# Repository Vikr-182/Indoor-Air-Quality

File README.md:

# Indoor-Air-Quality-Management
A complete Air Quality Index (AQI) sensing and management system designed and deployed in houses, to analyze the effects of outdoor and indoor events on indoor air quality, along with a Twitter service for constant updates.

## Components Involved
We list one by one, all the components involved in the usage -
- Using Microcontroller ESP8266
- Designing the 3D Enclosure
- Collecting and Analyzing Data
- Twitter Alerts
- OneM2M Usage

## Desigining the case
We designed the enclosure for our model using Autodesk Fusion360 and 3D printed it at Product Labs, IIITH.

## Collecting and Analyzing Data
- We were able to accurately predict the cooking times after carefully looking at the data - 

Notice the spike, which is representative of the cooking period in the kitchen.
- We specially collected our data during the Diwali festival and noticed anomalies in the data - 

Notice the read peak and slight normalization after due process.

## Twitter Alerts
Frequent time-to-time alerts were issued at this account [here](https://twitter.com/iiith_indoor). 

## OneM2M Usage
OneM2M was used as a common container for holding data and servicing REST APIs to and from.

## Software Used
- The following software were used in our project and will be required to successfully replicate our product -
```
Arduino IDE>=1.7 - Used for microcontrollers.
MATLAB ThingSpeak - IoT data visualization platform.
Autodesk Fusion360 - For editing and visualizing CAD models.
EaglePCB - For desigining and exporting PCB.
```
- Apart from the above, please include all the sensor libraries provided in the `src/sensor_libraries.zip`. Refer [here](https://www.arduino.cc/en/guide/libraries) for the tutorial for installation in the Arduino IDE.
- To install the python libaries, please use the command 
```
$: pip install --user -r requirements.txt
```

Created by - 
Bhavyajeet Singh, Pranav Kirsur and Vikrant Dewangan

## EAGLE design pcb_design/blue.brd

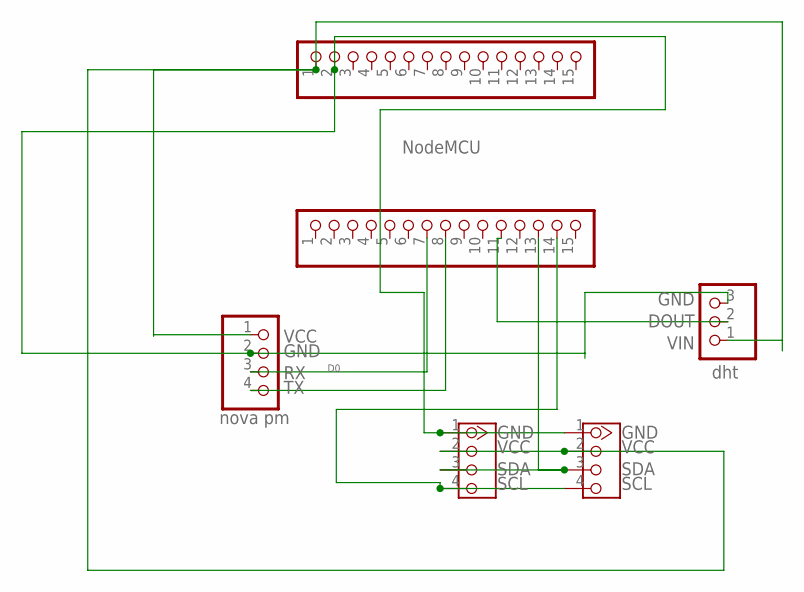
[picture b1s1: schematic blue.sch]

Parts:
J1, J2: 4P-2.0; HW4-2.0
JP1, JP2: PINHD-1X15; 1X15
JP3: PINHD-1X3; 1X03
JP4: PINHD-1X4; 1X04

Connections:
unnamed: JP1.11, JP3.2
unnamed: JP1.8, JP4.4
unnamed: JP1.7, JP4.3
unnamed: J1.2, J2.2, JP2.1, JP3.1, JP4.1
unnamed: J1.4, J2.4, JP1.14
unnamed: J1.3, J2.3, JP1.13
unnamed: J1.1, J2.1, JP2.2, JP3.3, JP4.2

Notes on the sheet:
dht
SCL
SDA
VCC
GND
VIN
DOUT
NodeMCU
nova pm

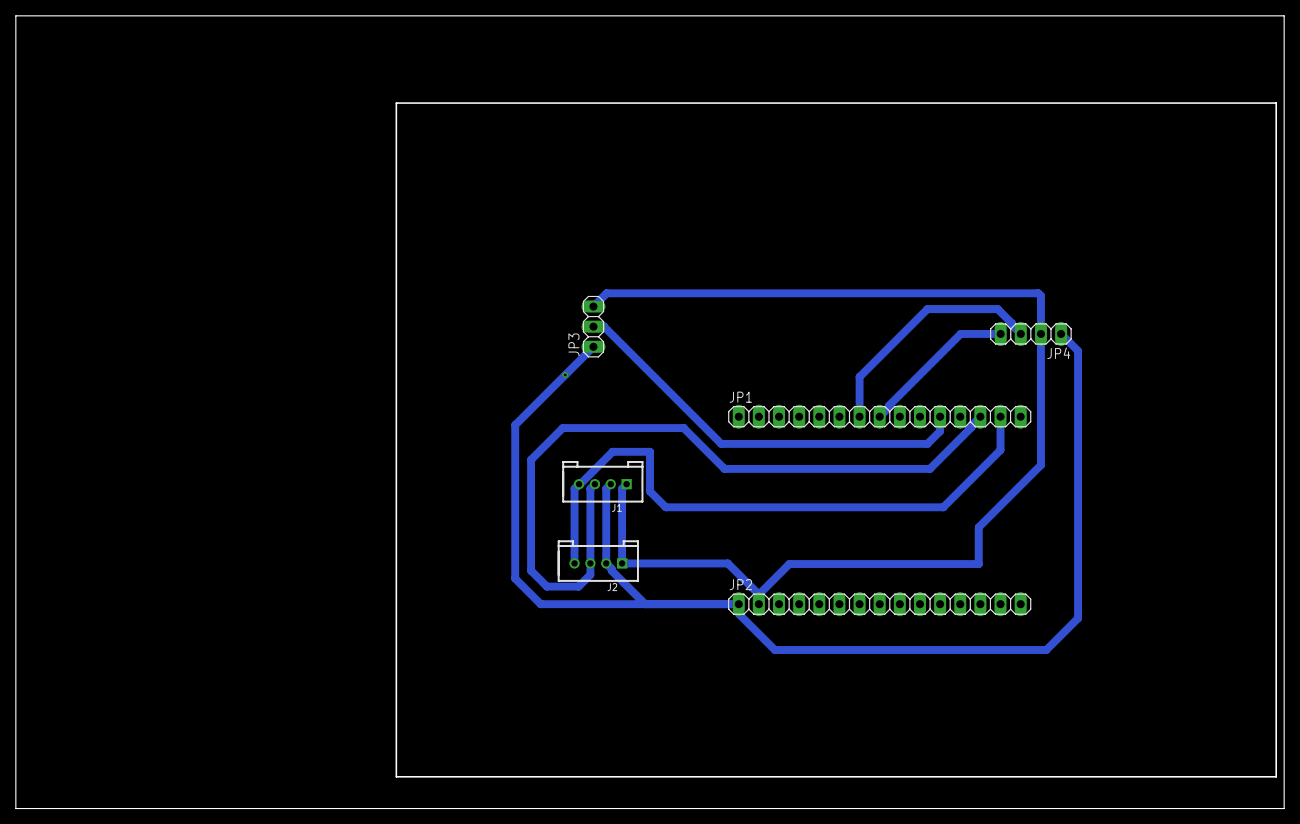
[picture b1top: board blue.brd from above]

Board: 2 copper layers, 160.0 x 100.0 mm, 6 parts (0 on the bottom side), 7 nets.

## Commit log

2019-10-13 added files
2019-10-15 added oneM2M code
2019-10-15 working code w/o oneM2M
2019-10-15 changed test.ino
2019-10-16 Added updates
2019-10-19 added working code
2019-10-20 added error correction code-backup_test.ino
2019-10-23 backup.ino contains the dumped code
2019-10-23 added pcb_design
2019-10-25 added sensor_libraries
2019-10-25 added script for pulling values
2019-10-25 added script
2019-10-25 added corrected code
2019-11-07 added second-node code
2019-11-07 added twitter-code
2019-11-07 added twitter code
2019-11-08 added all scripts
2019-11-21 added big codes
2019-11-21 added extra files
2019-11-22 added seperate channelwise tweets
2019-11-25 added latest combined data
2019-11-25 added the casing designs
2019-12-01 refactored code
2019-12-21 added indoor directory
2020-01-03 added eclipse code
2020-12-23 final commit
2020-12-23 restructured
2020-12-23 added imgs
2020-12-23 added
2020-12-23 changed size
2020-12-24 Create LICENSE
